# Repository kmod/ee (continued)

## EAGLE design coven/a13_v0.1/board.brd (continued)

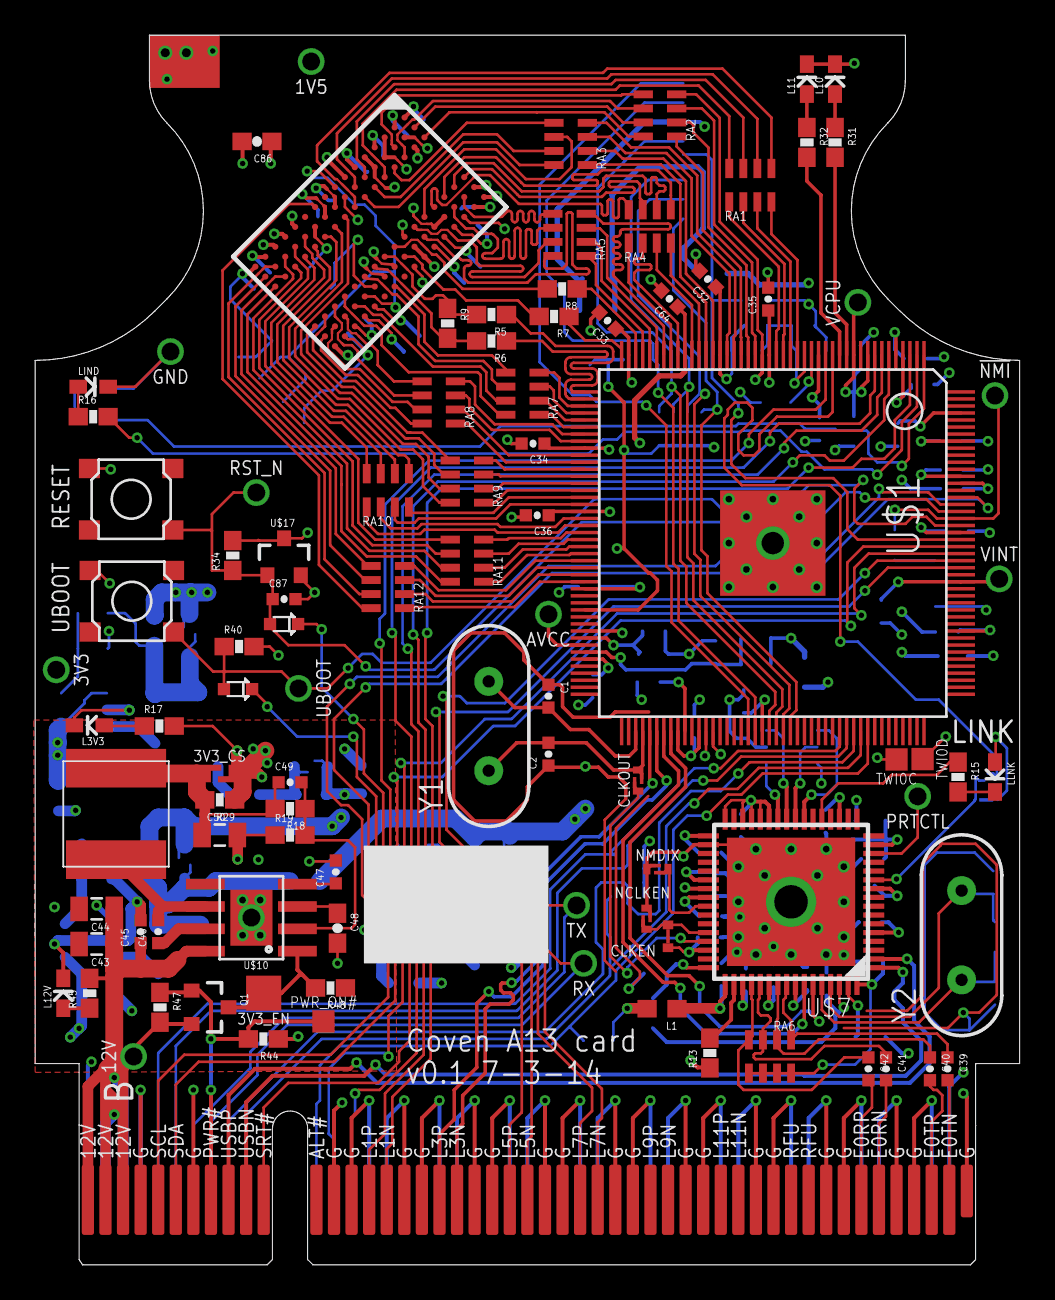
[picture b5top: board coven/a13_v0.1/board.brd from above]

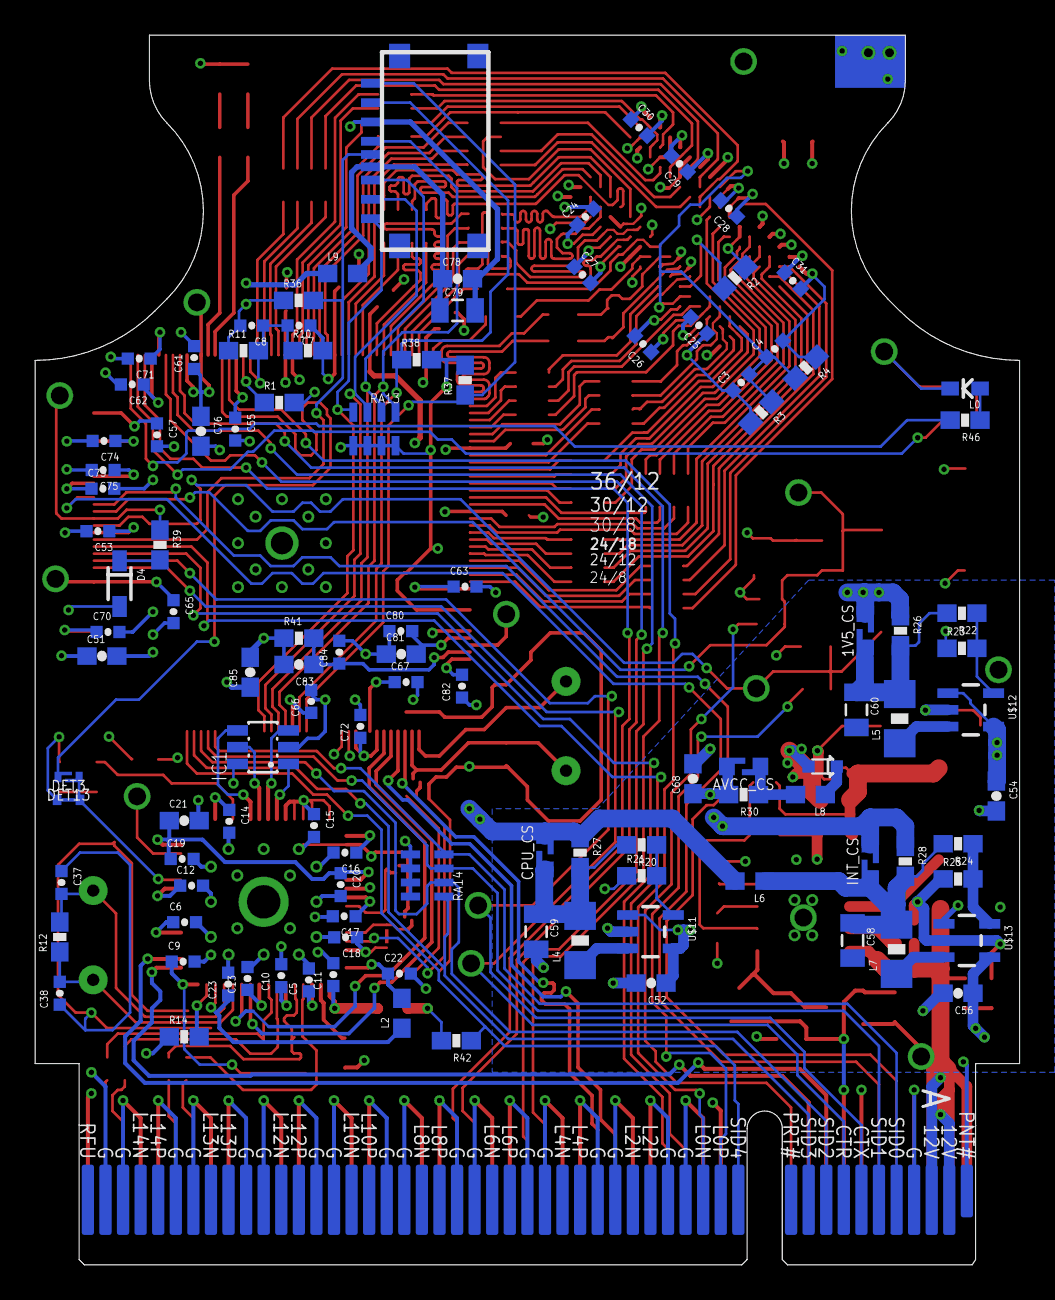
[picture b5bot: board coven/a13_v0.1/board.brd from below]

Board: 4 copper layers, 56.0 x 70.0 mm, 209 parts (111 on the bottom side), 208 nets.

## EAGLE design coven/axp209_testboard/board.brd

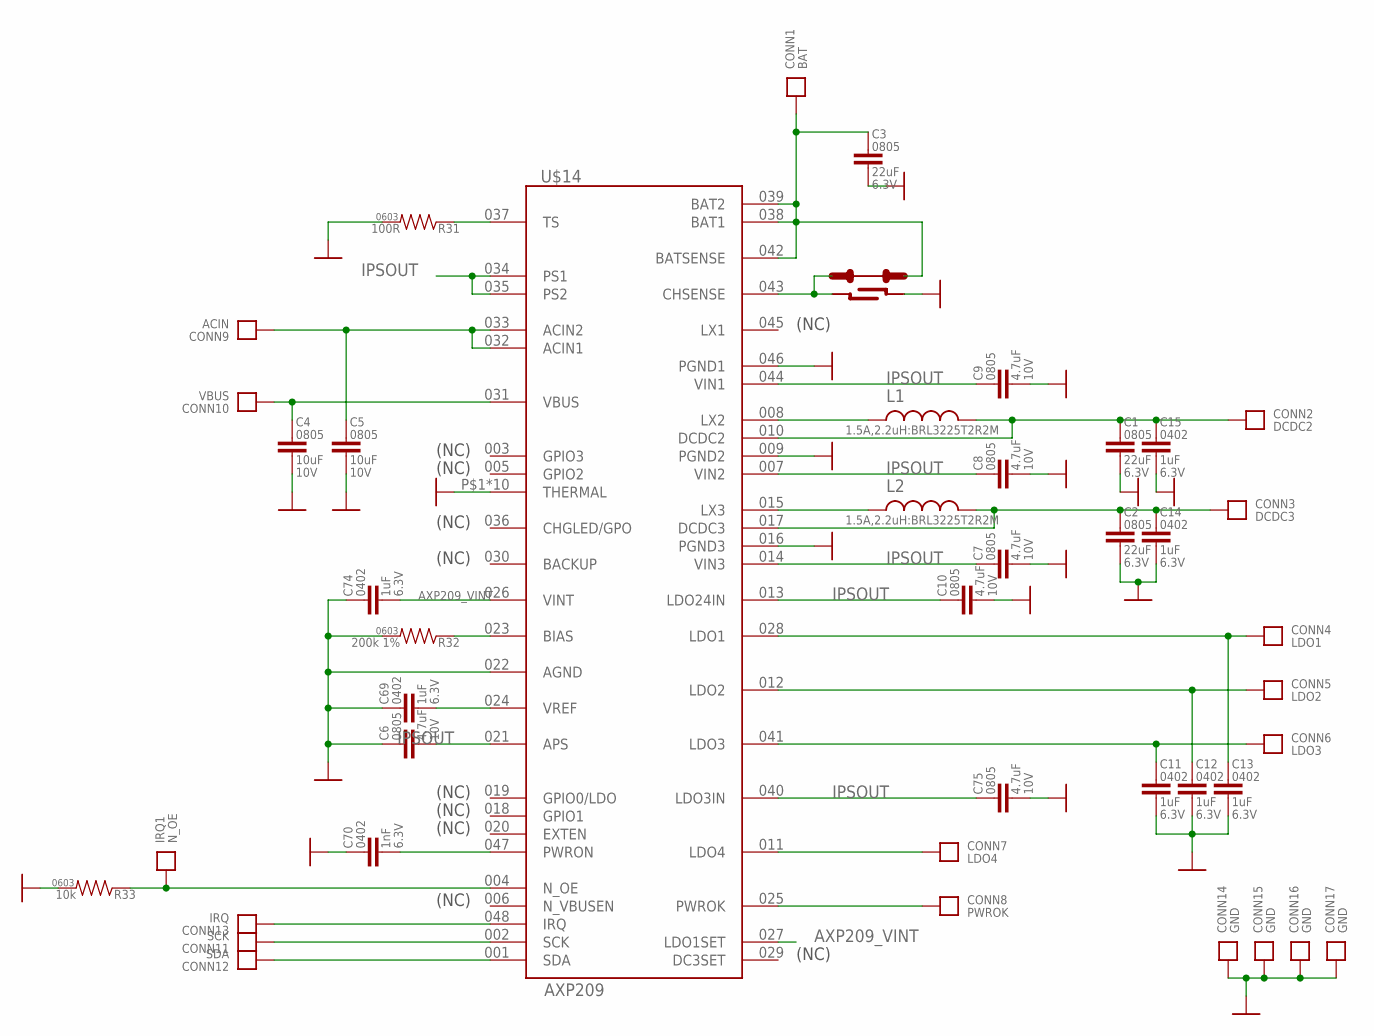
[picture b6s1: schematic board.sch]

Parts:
C1, C2, C3: 22uF; 0805
C4, C5: 10uF; 0805; VOLTAGE 10V
C6, C7, C8, C9, C10, C75: 4.7uF; 0805; VOLTAGE 10V
C11, C12, C13, C14, C15, C69, C74: 1uF; 0402-CAP
C70: 1nF; 0402-CAP
CONN1: BAT; HOLE_22AWG
CONN2: DCDC2; HOLE_22AWG
CONN3: DCDC3; HOLE_22AWG
CONN4: LDO1; HOLE_22AWG
CONN5: LDO2; HOLE_22AWG
CONN6: LDO3; HOLE_22AWG
CONN7: LDO4; HOLE_22AWG
CONN8: PWROK; HOLE_22AWG
CONN9: ACIN; HOLE_22AWG
CONN10: VBUS; HOLE_22AWG
CONN11: SCK; HOLE_22AWG
CONN12: SDA; HOLE_22AWG
CONN13: IRQ; HOLE_22AWG
CONN14, CONN15, CONN16, CONN17: GND; HOLE_22AWG
IRQ1: N_OE; HOLE_22AWG
L1, L2: 1.5A,2.2uH:BRL3225T2R2M; 1206
R31: 100R; 0603-RES
R32: 200k 1%; 0603-RES
R33: 10k; 0603-RES
SB7: SOLDER-BRIDGEOPEN; SOLDER-BRIDGE-OPEN
SB8: TRACE-CUT
U$14: AXP209; QFN48

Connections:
AXP209_NOE: IRQ1.P, R33.1, U$14.004 (N_OE)
AXP209_VINT: C74.2, U$14.026 (VINT), U$14.027 (LDO1SET)
GND: C1.2, C2.2, C3.2, C4.2, C5.2, C6.1, C7.2, C8.2, C9.2, C10.2, C11.2, C12.2, C13.2, C14.2, C15.2, C69.1, C70.1, C74.1, C75.2, CONN14.P, CONN15.P, CONN16.P, CONN17.P, R31.2, R32.2, R33.2, SB7.L1, SB7.L2, U$14.009 (PGND2), U$14.016 (PGND3), U$14.022 (AGND), U$14.046 (PGND1), U$14.P$1 (THERMAL), U$14.P$2 (THERMAL), U$14.P$3 (THERMAL), U$14.P$4 (THERMAL), U$14.P$5 (THERMAL), U$14.P$6 (THERMAL), U$14.P$7 (THERMAL), U$14.P$8 (THERMAL), U$14.P$9 (THERMAL), U$14.PAD (THERMAL)
IPSOUT: C6.2, C7.1, C8.1, C9.1, C10.1, C75.1, U$14.007 (VIN2), U$14.013 (LDO24IN), U$14.014 (VIN3), U$14.021 (APS), U$14.034 (PS1), U$14.035 (PS2), U$14.040 (LDO3IN), U$14.044 (VIN1)
LDO1: C13.1, CONN4.P, U$14.028 (LDO1)
LDO2: C12.1, CONN5.P, U$14.012 (LDO2)
LDO3: C11.1, CONN6.P, U$14.041 (LDO3)
LDO4: CONN7.P, U$14.011 (LDO4)
unnamed: C3.1, CONN1.P, SB8.R1, U$14.038 (BAT1), U$14.039 (BAT2), U$14.042 (BATSENSE)
unnamed: L1.1, U$14.008 (LX2)
unnamed: C1.1, C15.1, CONN2.P, L1.2, U$14.010 (DCDC2)
unnamed: L2.1, U$14.015 (LX3)
unnamed: C2.1, C14.1, CONN3.P, L2.2, U$14.017 (DCDC3)
unnamed: CONN13.P, U$14.048 (IRQ)
unnamed: CONN11.P, U$14.002 (SCK)
unnamed: CONN12.P, U$14.001 (SDA)
unnamed: CONN8.P, U$14.025 (PWROK)
unnamed: C69.2, U$14.024 (VREF)
unnamed: R31.1, U$14.037 (TS)
unnamed: C5.1, CONN9.P, U$14.032 (ACIN1), U$14.033 (ACIN2)
unnamed: C4.1, CONN10.P, U$14.031 (VBUS)
unnamed: R32.1, U$14.023 (BIAS)
unnamed: C70.2, U$14.047 (PWRON)
unnamed: SB7.R1, SB7.R2, SB8.L1, U$14.043 (CHSENSE)

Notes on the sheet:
(NC)

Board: 4 copper layers, 45 parts (0 on the bottom side), 24 nets, no tracks yet.
